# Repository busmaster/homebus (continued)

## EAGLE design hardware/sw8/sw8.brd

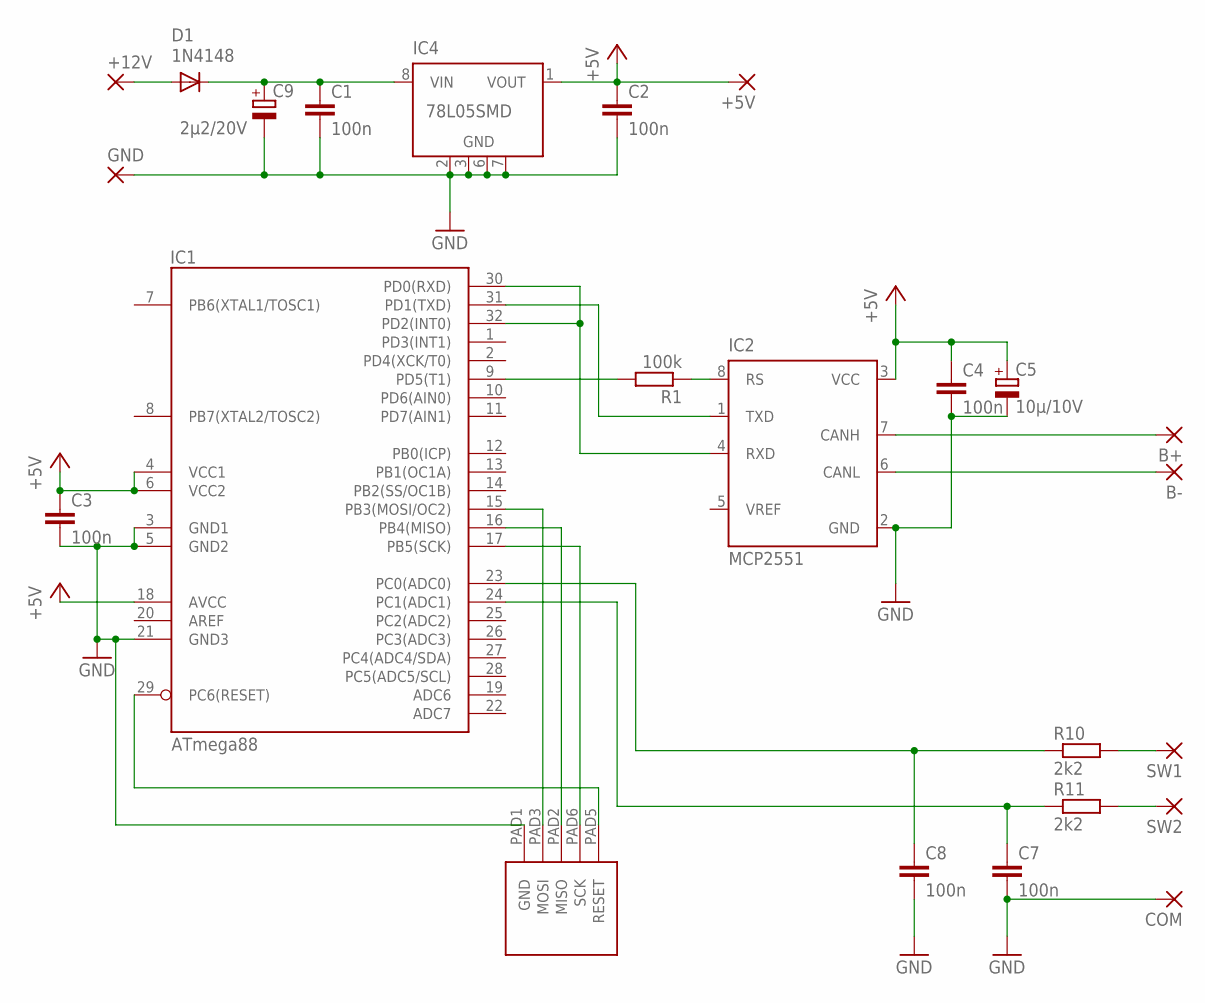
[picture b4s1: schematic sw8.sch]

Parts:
+5V, +12V: 1,6/0,8
B+: 1,6/0,8
B-: 1,6/0,8
C1, C2, C3, C4, C7, C8: 100n; C0603
C5: 10µ/10V; A/3216-18W
C9: 2µ2/20V; A/3216-18W
COM: 1,6/0,8
D1: 1N4148; SOD80C
GND: 1,6/0,8
IC1: ATmega88; TQFP32-08
IC2: MCP2551; SO8
IC4: 78L05SMD; SO08
R1: 100k; R0603
R10, R11: 2k2; R0603
SW1, SW2: 1,6/0,8
U$1: ATMEL_ISP

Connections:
+5V: +5V.1, C2.1, C3.1, C4.1, C5.+, IC1.4 (VCC1), IC1.6 (VCC2), IC1.18 (AVCC), IC2.3 (VCC), IC4.1 (VOUT)
AREF: IC1.20 (AREF)
GND: C1.2, C2.2, C3.2, C4.2, C5.-, C7.2, C8.2, C9.-, COM.1, GND.1, IC1.3 (GND1), IC1.5 (GND2), IC1.21 (GND3), IC2.2 (GND), IC4.2 (GND), IC4.3 (GND), IC4.6 (GND), IC4.7 (GND), U$1.PAD1 (GND)
MISO: IC1.16 (PB4(MISO)), U$1.PAD2 (MISO)
MOSI: IC1.15 (PB3(MOSI/OC2)), U$1.PAD3 (MOSI)
unnamed: B+.1, IC2.7 (CANH)
unnamed: B-.1, IC2.6 (CANL)
unnamed: IC1.31 (PD1(TXD)), IC2.1 (TXD)
unnamed: IC1.30 (PD0(RXD)), IC1.32 (PD2(INT0)), IC2.4 (RXD)
unnamed: IC2.8 (RS), R1.1
unnamed: IC1.9 (PD5(T1)), R1.2
unnamed: C1.1, C9.+, D1.C, IC4.8 (VIN)
unnamed: C7.1, IC1.24 (PC1(ADC1)), R11.1
unnamed: C8.1, IC1.23 (PC0(ADC0)), R10.1
unnamed: +12V.1, D1.A
unnamed: R10.2, SW1.1
unnamed: R11.2, SW2.1
RESET: IC1.29 (PC6(RESET)), U$1.PAD5 (RESET)
SCK: IC1.17 (PB5(SCK)), U$1.PAD6 (SCK)

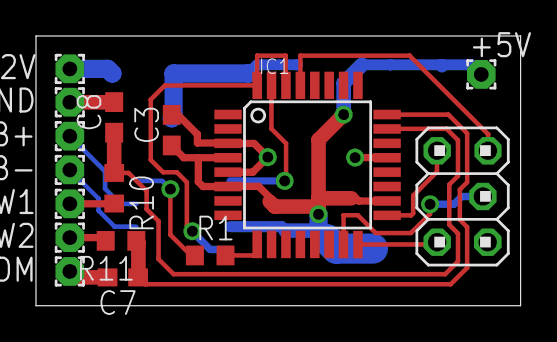
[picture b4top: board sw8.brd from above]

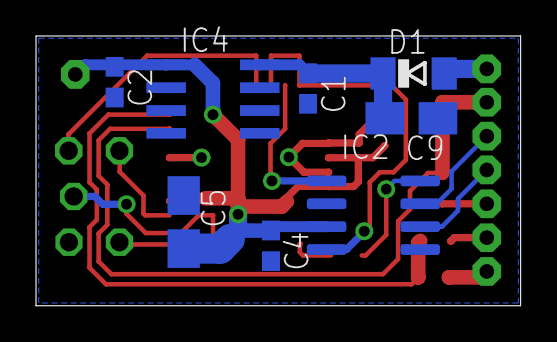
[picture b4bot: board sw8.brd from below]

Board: 2 copper layers, 26.9 x 15.0 mm, 24 parts (8 on the bottom side), 18 nets.

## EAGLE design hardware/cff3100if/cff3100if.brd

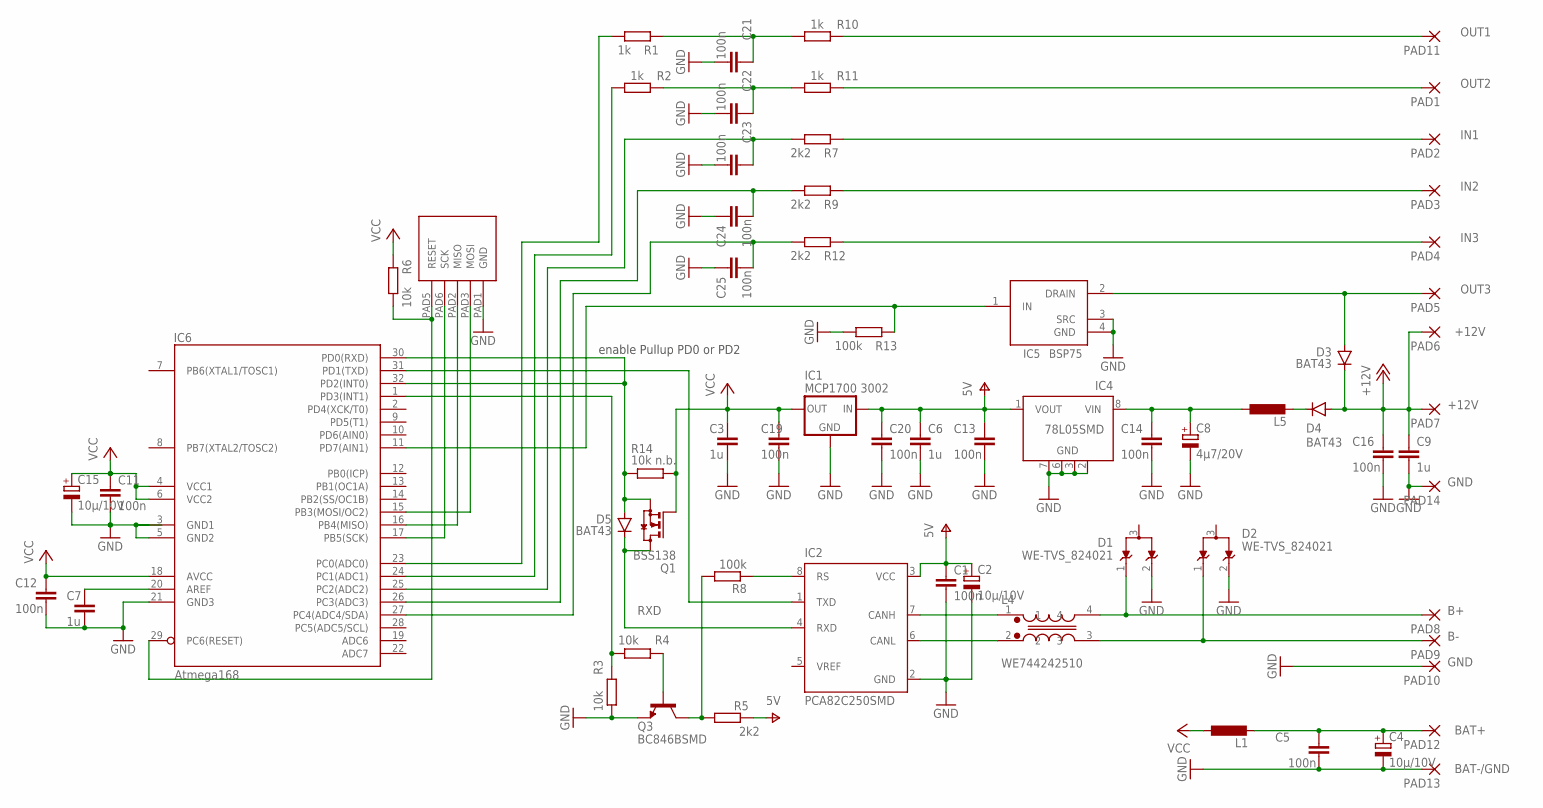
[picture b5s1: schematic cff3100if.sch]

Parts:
C1, C5, C11, C12, C13, C14, C16, C19, C20, C21, C22, C23, C24, C25: 100n; C0603
C2, C4, C15: 10µ/10V; A/3216-18W
C3, C6, C7, C9: 1u; C1206
C8: 4µ7/20V; A/3216-18W
D1, D2: WE-TVS_824021; WE-TVS_SOT23-3L
D3, D4, D5: BAT43; MINIMELF
IC1: MCP1700 3002; SOT23
IC2: PCA82C250SMD; SO8
IC4: 78L05SMD; SO08
IC5: BSP75; SOT223
IC6: Atmega168; TQFP32-08
L1, L5: L-EUL1806; L1806
L4: WE744242510; WE-SLM
PAD1, PAD2, PAD3, PAD4, PAD5, PAD7, PAD8, PAD9, PAD10, PAD11, PAD14: 1,6/0,9
PAD6: +12V; 1,6/0,9
PAD12: BAT+; 1,6/0,9
PAD13: BAT-/GND; 1,6/0,9
Q1: BSS138; SOT23
Q3: BC846BSMD; SOT23
R1, R2, R10, R11: 1k; R0603
R3, R4, R6: 10k; R0603
R5, R7, R9, R12: 2k2; R0603
R8, R13: 100k; R0603
R14: 10k n.b.; R0603
U$2: ATMEL_ISP

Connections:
+12V: C9.1, C16.1, D3.C, D4.A, PAD6.1, PAD7.1
B+: D1.1, L4.4, PAD8.1
B-: D2.1, L4.3, PAD9.1
GND: C1.2, C2.-, C3.2, C4.-, C5.2, C6.2, C7.2, C8.-, C9.2, C11.2, C12.2, C13.2, C14.2, C15.-, C16.2, C19.2, C20.2, C21.2, C22.2, C23.2, C24.1, C25.1, D1.2, D2.2, IC1.1 (GND), IC2.2 (GND), IC4.2 (GND), IC4.3 (GND), IC4.6 (GND), IC4.7 (GND), IC5.3 (SRC), IC5.4 (GND), IC6.3 (GND1), IC6.5 (GND2), IC6.21 (GND3), PAD10.1, PAD13.1, PAD14.1, Q3.2 (E), R3.2, R13.2, U$2.PAD1 (GND)
IN1: PAD2.1, R7.1
IN2: PAD3.1, R9.1
IN3: PAD4.1, R12.1
unnamed: IC6.29 (PC6(RESET)), R6.2, U$2.PAD5 (RESET)
unnamed: C4.+, C5.1, L1.2, PAD12.1
unnamed: IC6.1 (PD3(INT1)), R3.1, R4.2
unnamed: D4.C, L5.2
unnamed: IC6.23 (PC0(ADC0)), R1.2
unnamed: IC6.24 (PC1(ADC1)), R2.2
unnamed: C21.1, R1.1, R10.2
unnamed: C22.1, R2.1, R11.2
unnamed: IC2.7 (CANH), L4.1
unnamed: Q3.3 (C), R5.1, R8.2
unnamed: Q3.1 (B), R4.1
unnamed: C23.1, IC6.25 (PC2(ADC2)), R7.2
unnamed: C24.2, IC6.26 (PC3(ADC3)), R9.2
unnamed: C25.2, IC6.27 (PC4(ADC4/SDA)), R12.2
unnamed: IC2.1 (TXD), IC6.31 (PD1(TXD))
unnamed: IC2.6 (CANL), L4.2
unnamed: D5.A, IC6.30 (PD0(RXD)), IC6.32 (PD2(INT0)), Q1.2 (S), R14.2
unnamed: IC5.1 (IN), IC6.11 (PD7(AIN1)), R13.1
unnamed: IC6.17 (PB5(SCK)), U$2.PAD6 (SCK)
unnamed: IC6.15 (PB3(MOSI/OC2)), U$2.PAD3 (MOSI)
unnamed: IC6.16 (PB4(MISO)), U$2.PAD2 (MISO)
unnamed: C7.1, IC6.20 (AREF)
unnamed: IC2.8 (RS), R8.1
unnamed: C8.+, C14.1, IC4.8 (VIN), L5.1
OUT1: PAD11.1, R10.1
OUT2: PAD1.1, R11.1
OUT3: D3.A, IC5.2 (DRAIN), PAD5.1
RXD: D5.C, IC2.4 (RXD), Q1.3 (D)
V+: C1.1, C2.+, C6.1, C13.1, C20.1, IC1.3 (IN), IC2.3 (VCC), IC4.1 (VOUT), R5.2
VCC: C3.1, C11.1, C12.1, C15.+, C19.1, IC1.2 (OUT), IC6.4 (VCC1), IC6.6 (VCC2), IC6.18 (AVCC), L1.1, Q1.1 (G), R6.1, R14.1

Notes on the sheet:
enable Pullup PD0 or PD2

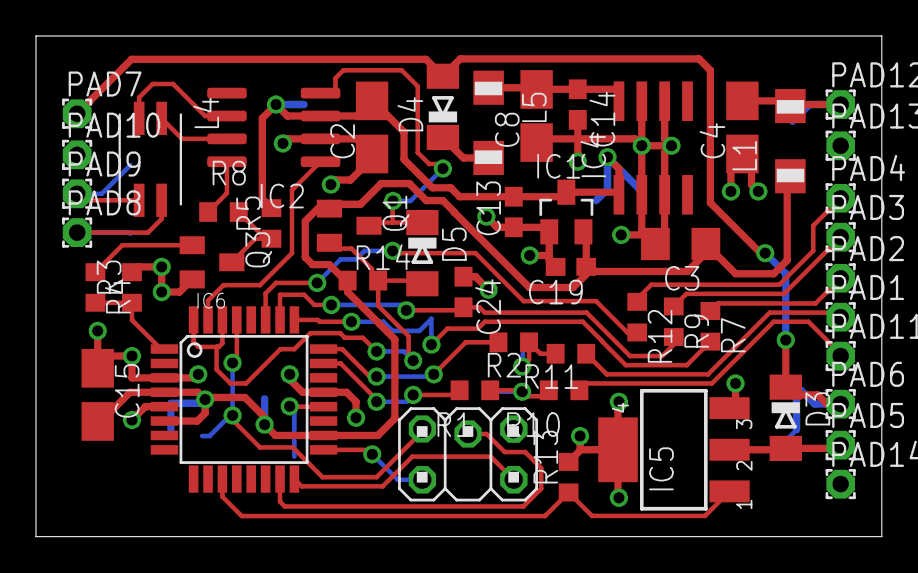
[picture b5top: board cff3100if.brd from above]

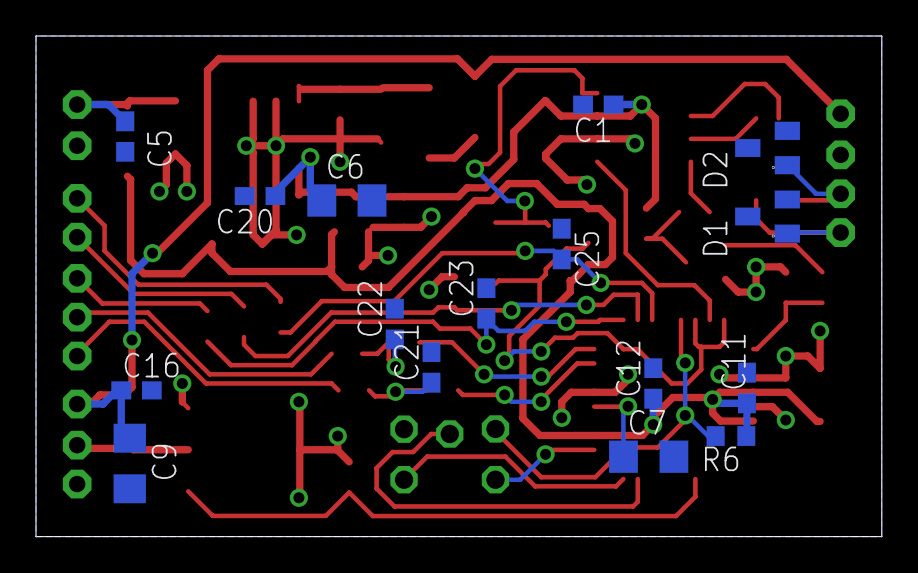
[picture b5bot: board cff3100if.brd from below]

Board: 2 copper layers, 47.0 x 27.8 mm, 66 parts (16 on the bottom side), 37 nets.

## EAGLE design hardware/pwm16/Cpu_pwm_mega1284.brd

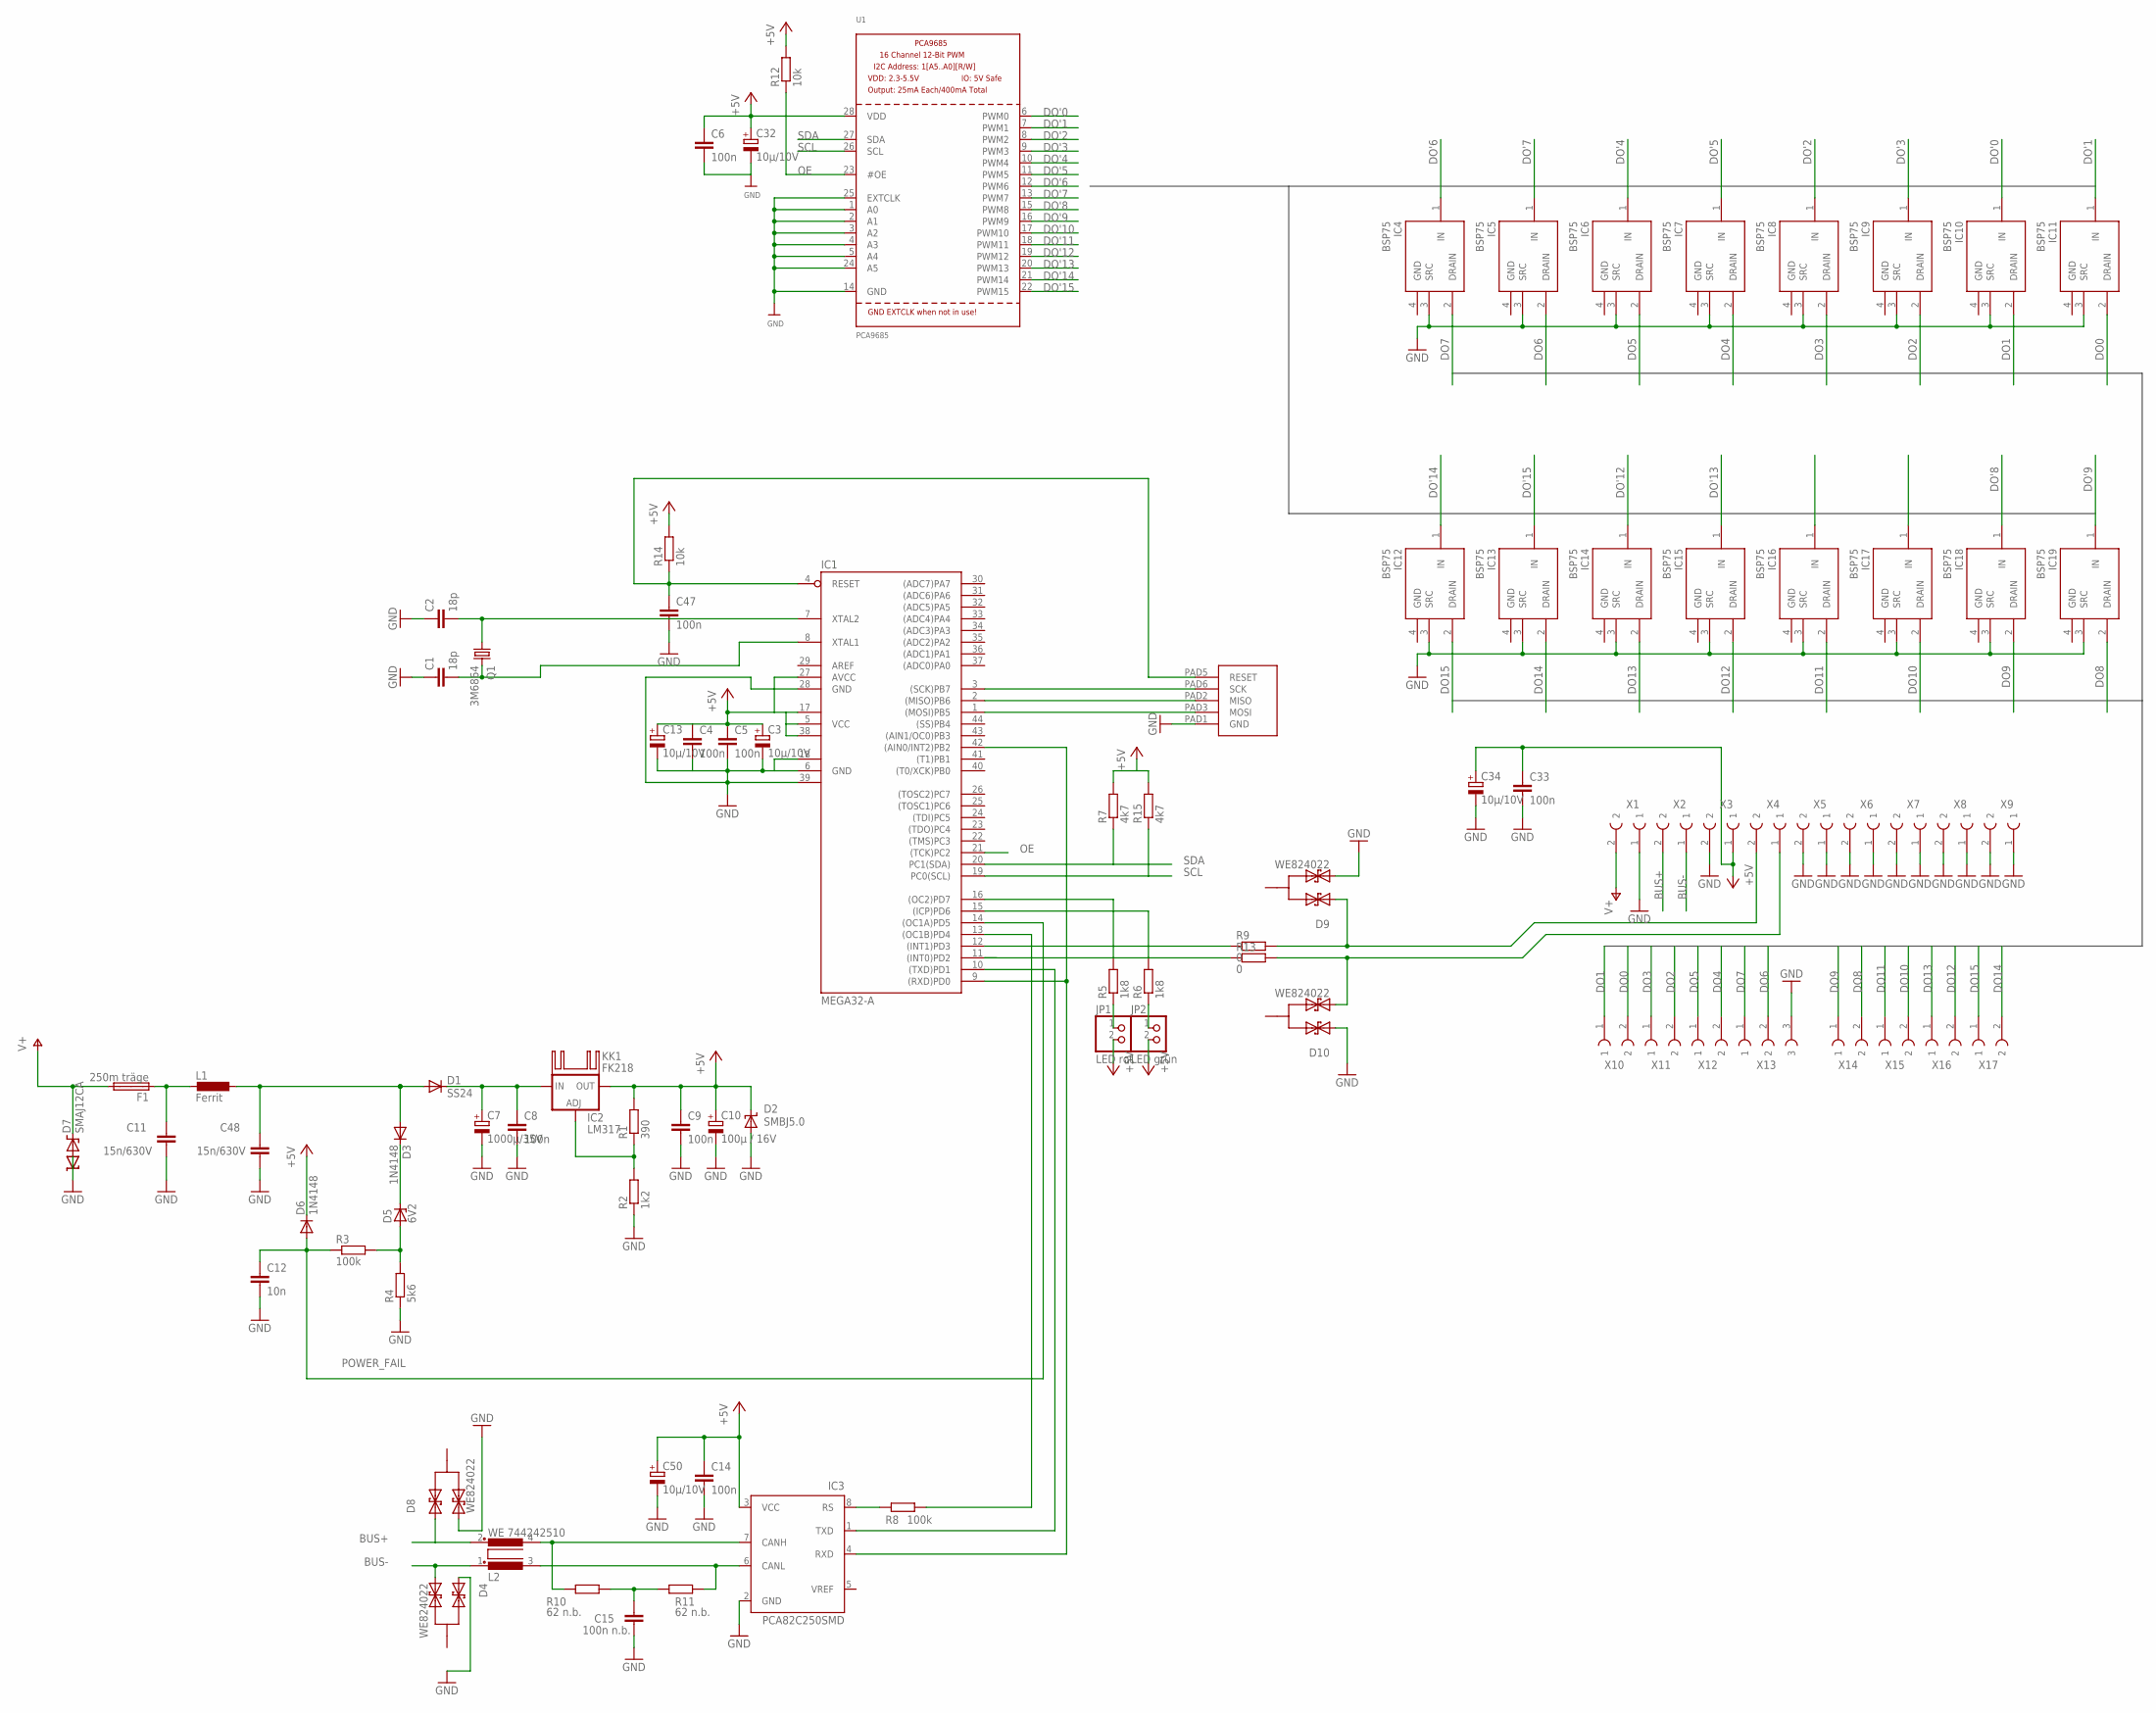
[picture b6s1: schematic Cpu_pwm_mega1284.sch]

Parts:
C1, C2: 18p; C0603K
C3, C13, C32, C34, C50: 10µ/10V; A/3216-18W
C4, C5, C6, C8, C9, C14, C33, C47: 100n; C0603K
C7: 1000µ/35V; E5-13
C10: 100µ / 16V; SMC_D
C11, C48: 15n/630V; C1210K
C12: 10n; C0603K
C15: 100n n.b.; C0603K
D1: SS24; SMB
D2: SMBJ5.0; SMBJ
D3, D6: 1N4148; MINIMELF
D4, D8, D9, D10: WE824022; SOT23
D5: 6V2; SOD80C
D7: SMAJ12CA; DO-214AC
F1: 250m träge; SHK20L
IC1: MEGA32-A; TQFP44
IC2: LM317; 317TS
IC3: PCA82C250SMD; SO8
IC4, IC5, IC6, IC7, IC8, IC9, IC10, IC11, IC12, IC13, IC14, IC15, IC16, IC17, IC18, IC19: BSP75; SOT223
JP1: LED rot; 1X02
JP2: LED grün; 1X02
KK1: FK218
L1: Ferrit; L1806
L2: WE 744242510; 744242510
Q1: 3M6864; HC49UP
R1: 390; R0603
R2: 1k2; R0603
R3, R8: 100k; R0603
R4: 5k6; R0603
R5, R6: 1k8; R0603
R7, R15: 4k7; R0603
R9, R13: 0; R0603
R10, R11: 62 n.b.; R1210
R12, R14: 10k; R0603
U1: PCA9685; TSSOP28
U$1: ATMEL_ISP
X1, X2, X3, X4, X5, X6, X7, X8, X9, X10, X11, X12, X14, X15, X16, X17: AR-KLEMME_508_2POLPTR; W237-2E
X13: AR-KLEMME_508_3POLPTR; W237-3E

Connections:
+5V: C3.+, C4.1, C5.1, C6.1, C9.1, C10.+, C13.+, C14.1, C32.+, C33.1, C34.+, C50.+, D2.C, D6.C, IC1.5 (VCC), IC1.17 (VCC1), IC1.27 (AVCC), IC1.38 (VCC2), IC2.2 (OUT), IC3.3 (VCC), JP1.2, JP2.2, R1.2, R7.2, R12.2, R14.2, R15.2, U1.28 (VDD), X3.1
/RESET: C47.1, IC1.4 (RESET), R14.1, U$1.PAD5 (RESET)
BUS+: D8.1, L2.2, X2.2
BUS-: D4.2, L2.1, X2.1
DO0: IC11.2 (DRAIN), X10.2
DO1: IC10.2 (DRAIN), X10.1
DO2: IC9.2 (DRAIN), X11.2
DO3: IC8.2 (DRAIN), X11.1
DO4: IC7.2 (DRAIN), X12.2
DO5: IC6.2 (DRAIN), X12.1
DO6: IC5.2 (DRAIN), X13.2
DO7: IC4.2 (DRAIN), X13.1
DO8: IC19.2 (DRAIN), X14.2
DO9: IC18.2 (DRAIN), X14.1
DO10: IC17.2 (DRAIN), X15.2
DO11: IC16.2 (DRAIN), X15.1
DO12: IC15.2 (DRAIN), X16.2
DO13: IC14.2 (DRAIN), X16.1
DO14: IC13.2 (DRAIN), X17.2
DO15: IC12.2 (DRAIN), X17.1
DO'0: IC10.1 (IN), U1.6 (PWM0)
DO'1: IC11.1 (IN), U1.7 (PWM1)
DO'2: IC8.1 (IN), U1.8 (PWM2)
DO'3: IC9.1 (IN), U1.9 (PWM3)
DO'4: IC6.1 (IN), U1.10 (PWM4)
DO'5: IC7.1 (IN), U1.11 (PWM5)
DO'6: IC4.1 (IN), U1.12 (PWM6)
DO'7: IC5.1 (IN), U1.13 (PWM7)
DO'8: IC18.1 (IN), U1.15 (PWM8)
DO'9: IC19.1 (IN), U1.16 (PWM9)
DO'10: IC16.1 (IN), U1.17 (PWM10)
DO'11: IC17.1 (IN), U1.18 (PWM11)
DO'12: IC14.1 (IN), U1.19 (PWM12)
DO'13: IC15.1 (IN), U1.20 (PWM13)
DO'14: IC12.1 (IN), U1.21 (PWM14)
DO'15: IC13.1 (IN), U1.22 (PWM15)
GND: C1.1, C2.1, C3.-, C4.2, C5.2, C6.2, C7.-, C8.2, C9.2, C10.-, C11.2, C12.2, C13.-, C14.2, C15.1, C32.-, C33.2, C34.-, C47.2, C48.2, C50.-, D2.A, D4.1, D7.A, D8.2, D9.2, D10.1, IC1.6 (GND), IC1.18 (GND1), IC1.28 (GND), IC1.39 (GND2), IC3.2 (GND), IC4.3 (SRC), IC5.3 (SRC), IC6.3 (SRC), IC7.3 (SRC), IC8.3 (SRC), IC9.3 (SRC), IC10.3 (SRC), IC11.3 (SRC), IC12.3 (SRC), IC13.3 (SRC), IC14.3 (SRC), IC15.3 (SRC), IC16.3 (SRC), IC17.3 (SRC), IC18.3 (SRC), IC19.3 (SRC), R2.1, R4.1, U1.1 (A0), U1.2 (A1), U1.3 (A2), U1.4 (A3), U1.5 (A4), U1.14 (GND), U1.24 (A5), U1.25 (EXTCLK), U$1.PAD1 (GND), X1.1, X3.2, X5.1, X5.2, X6.1, X6.2, X7.1, X7.2, X8.1, X8.2, X9.1, X9.2, X13.3
MISO: IC1.2 ((MISO)PB6), U$1.PAD2 (MISO)
MOSI: IC1.1 ((MOSI)PB5), U$1.PAD3 (MOSI)
unnamed: C11.1, F1.1A, L1.2
unnamed: D3.C, D5.C
unnamed: D5.A, R3.2, R4.2
unnamed: C1.2, IC1.8 (XTAL1), Q1.2
unnamed: C2.2, IC1.7 (XTAL2), Q1.1
unnamed: IC3.8 (RS), R8.2
unnamed: IC1.13 ((OC1B)PD4), R8.1
unnamed: IC2.1 (ADJ), R1.1, R2.2
unnamed: IC3.6 (CANL), L2.3, R11.1
unnamed: IC3.7 (CANH), L2.4, R10.2
unnamed: C48.1, D1.A, D3.A, L1.1
unnamed: C7.+, C8.1, D1.C, IC2.3 (IN)
unnamed: IC1.11 ((INT0)PD2), R13.1
unnamed: IC1.12 ((INT1)PD3), R9.1
unnamed: C15.2, R10.1, R11.2
unnamed: JP1.1, R5.1
unnamed: JP2.1, R6.1
unnamed: IC1.16 ((OC2)PD7), R5.2
unnamed: IC1.15 ((ICP)PD6), R6.2
OE: IC1.21 ((TCK)PC2), R12.1, U1.23 (#OE)
POWER_FAIL: C12.1, D6.A, IC1.14 ((OC1A)PD5), R3.1
RXD: IC1.9 ((RXD)PD0), IC1.42 ((AIN0/INT2)PB2), IC3.4 (RXD)
RXD1: D10.2, R13.2, X4.1
SCK: IC1.3 ((SCK)PB7), U$1.PAD6 (SCK)
SCL: IC1.19 (PC0(SCL)), R15.1, U1.26 (SCL)
SDA: IC1.20 (PC1(SDA)), R7.1, U1.27 (SDA)
TSD1: D9.1, R9.2, X4.2
TXD: IC1.10 ((TXD)PD1), IC3.1 (TXD)
V+: D7.C, F1.2A, X1.2

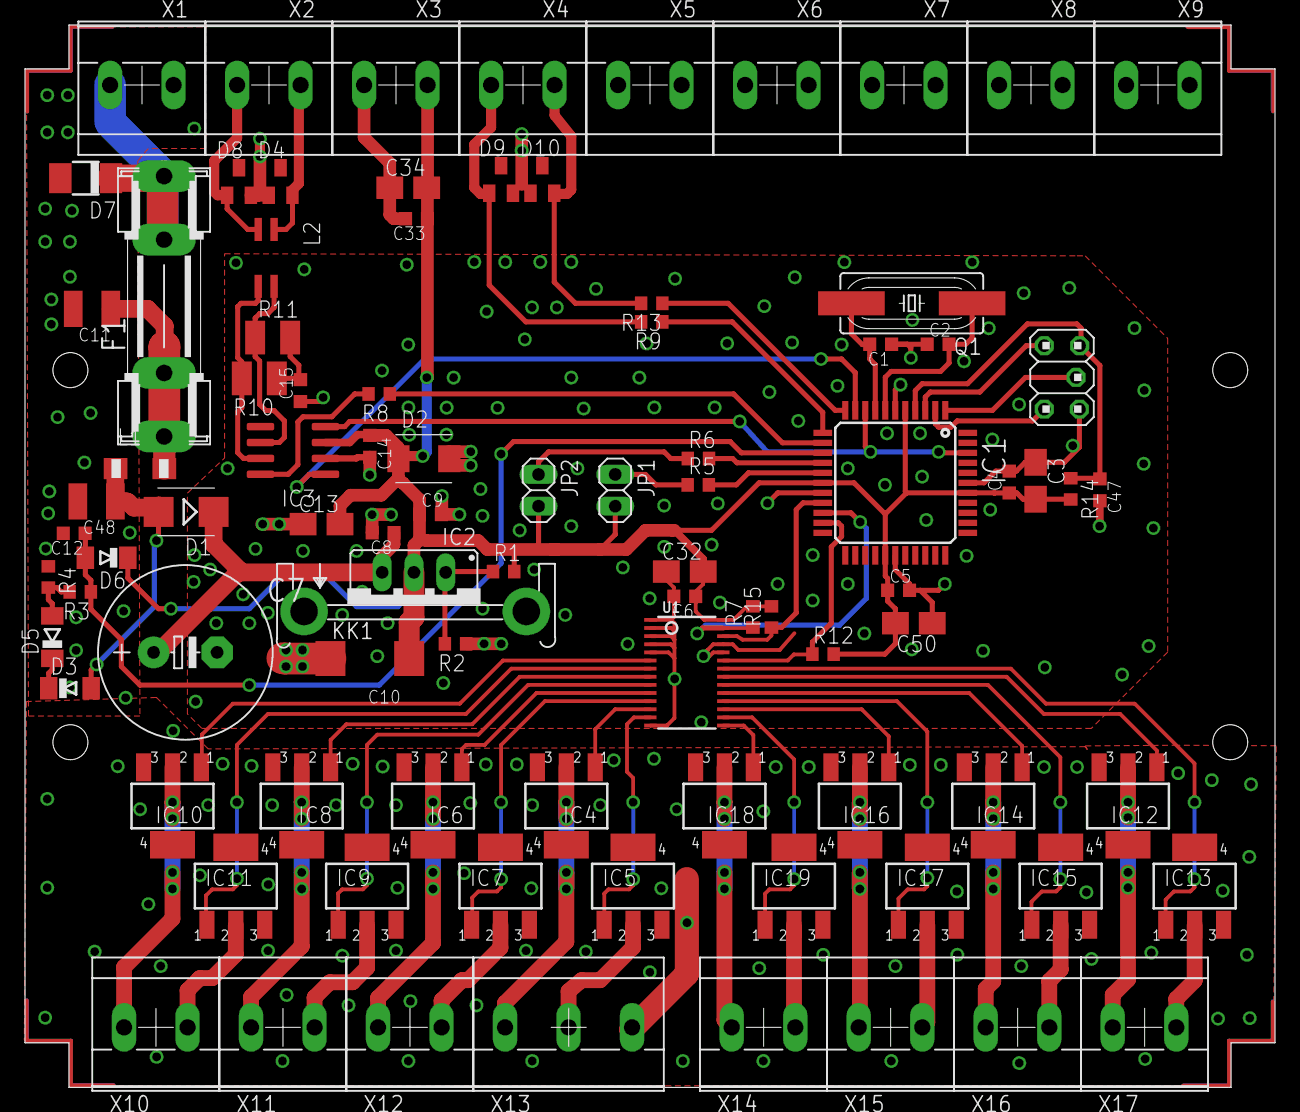
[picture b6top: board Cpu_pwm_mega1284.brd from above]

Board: 2 copper layers, 100.0 x 85.0 mm, 92 parts (0 on the bottom side), 68 nets.

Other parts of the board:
U$3: GEHÄUSE_MR6

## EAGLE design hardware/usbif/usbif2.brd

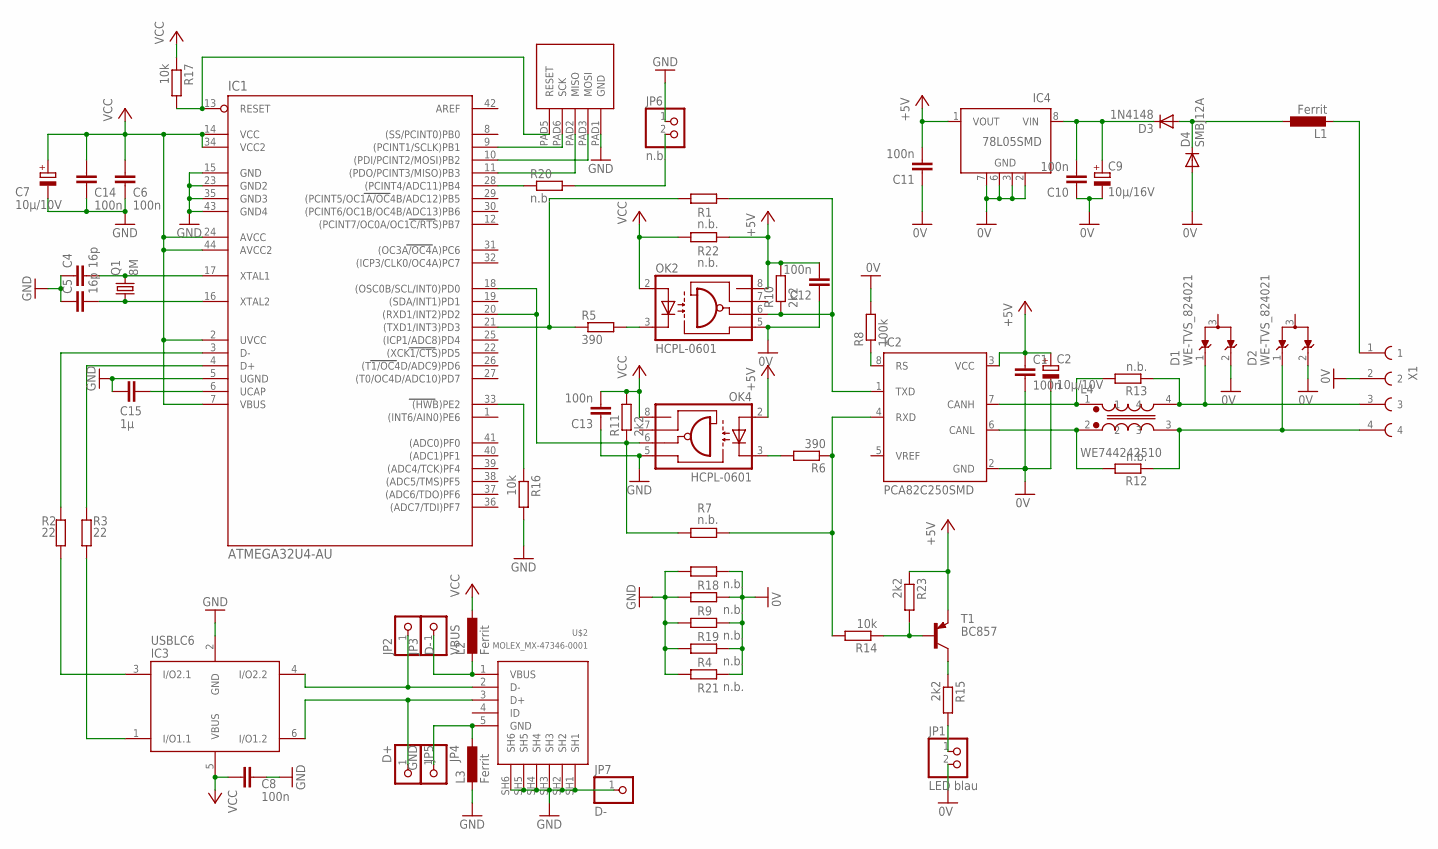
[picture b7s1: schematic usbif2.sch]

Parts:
C1, C6, C8, C10, C11, C12, C13, C14: 100n; C0603
C2, C7: 10µ/10V; A/3216-18W
C4, C5: 16p; C0603
C9: 10µ/16V; A/3216-18W
C15: 1µ; C1210K
D1, D2: WE-TVS_824021; WE-TVS_SOT23-3L
D3: 1N4148; SOD80C
D4: SMBJ12A; SMB
IC1: ATMEGA32U4-AU; TQFP44
IC2: PCA82C250SMD; SO8
IC3: USBLC6; SOT23-6L
IC4: 78L05SMD; SO08
JP1: LED blau; 1X02
JP2, JP7: D-; 1X01
JP3: VBUS; 1X01
JP4: GND; 1X01
JP5: D+; 1X01
JP6: n.b.; 1X02
L1, L2, L3: Ferrit; L1806
L4: WE744242510; WE-SLM
OK2, OK4: HCPL-0601; SOIC08
Q1: 8M; SM49
R1, R4, R7, R9, R18, R19, R21, R22: n.b.; MINI_MELF-0204R
R2, R3: 22; R0603
R5, R6: 390; R0603
R8: 100k; R0603
R10, R11, R15, R23: 2k2; R0603
R12, R13, R20: n.b.; R0603
R14, R16, R17: 10k; R0603
T1: BC857; SOT323-BEC
U$1: ATMEL_ISP
U$2: MOLEX_MX-47346-0001
X1: DEGSON_15EDGRC-3.5_4

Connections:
0V: C1.2, C2.-, C9.-, C10.1, C11.1, C12.1, D1.2, D2.2, D4.A, IC2.2 (GND), IC4.2 (GND), IC4.3 (GND), IC4.6 (GND), IC4.7 (GND), JP1.2, OK2.5 (GND), R4.1, R8.2, R9.1, R18.1, R19.1, R21.1, X1.2
#RESET: IC1.13 (RESET), R17.2, U$1.PAD5 (RESET)
+5V: C1.1, C2.+, C11.2, C12.2, IC2.3 (VCC), IC4.1 (VOUT), OK2.8 (VCC), OK4.2 (A), R10.2, R22.1, R23.1, T1.E
+12V: L1.2, X1.1
B+: D1.1, L4.4, R13.1, X1.3
B-: D2.1, L4.3, R12.1, X1.4
D+: IC3.6 (I/O1.2), JP5.1, U$2.3 (D+)
D-: IC3.4 (I/O2.2), JP2.1, U$2.2 (D-)
GND: C4.1, C5.1, C6.1, C7.-, C8.1, C13.1, C14.1, C15.2, IC1.5 (UGND), IC1.15 (GND), IC1.23 (GND2), IC1.35 (GND3), IC1.43 (GND4), IC3.2 (GND), JP6.1, JP7.1, L3.2, OK4.5 (GND), R4.2, R9.2, R16.2, R18.2, R19.2, R21.2, U$1.PAD1 (GND), U$2.SH1, U$2.SH2, U$2.SH3, U$2.SH4, U$2.SH5, U$2.SH6
unnamed: OK2.3 (C), R5.2
unnamed: IC1.18 ((OSC0B/SCL/INT0)PD0), IC1.20 ((RXD1/INT2)PD2), OK4.6 (VO), R7.2, R11.1
unnamed: IC2.1 (TXD), OK2.6 (VO), R1.1, R10.1
unnamed: IC2.4 (RXD), R6.1, R7.1, R14.2
unnamed: IC1.10 ((PDI/PCINT2/MOSI)PB2), U$1.PAD3 (MOSI)
unnamed: IC1.11 ((PDO/PCINT3/MISO)PB3), U$1.PAD2 (MISO)
unnamed: IC1.9 ((PCINT1/SCLK)PB1), U$1.PAD6 (SCK)
unnamed: IC1.4 (D+), R3.1
unnamed: IC2.7 (CANH), L4.1, R13.2
unnamed: C15.1, IC1.6 (UCAP)
unnamed: IC1.3 (D-), R2.1
unnamed: IC3.1 (I/O1.1), R3.2
unnamed: IC3.3 (I/O2.1), R2.2
unnamed: C4.2, IC1.17 (XTAL1), Q1.2
unnamed: C5.2, IC1.16 (XTAL2), Q1.1
unnamed: IC2.6 (CANL), L4.2, R12.2
unnamed: JP6.2, R20.2
unnamed: IC1.28 ((PCINT4/ADC11)PB4), R20.1
unnamed: D3.A, D4.C, L1.1
unnamed: C9.+, C10.2, D3.C, IC4.8 (VIN)
unnamed: OK4.3 (C), R6.2
unnamed: R15.1, T1.C
unnamed: IC1.33 ((HWB)PE2), R16.1
unnamed: R14.1, R23.2, T1.B
unnamed: JP1.1, R15.2
unnamed: IC2.8 (RS), R8.1
unnamed: JP4.1, L3.1, U$2.5 (GND)
unnamed: IC1.21 ((TXD1/INT3)PD3), R1.2, R5.1
VBUS: JP3.1, L2.2, U$2.1 (VBUS)
VCC: C6.2, C7.+, C8.2, C13.2, C14.2, IC1.2 (UVCC), IC1.7 (VBUS), IC1.14 (VCC), IC1.24 (AVCC), IC1.34 (VCC2), IC1.44 (AVCC2), IC3.5 (VBUS), L2.1, OK2.2 (A), OK4.8 (VCC), R11.2, R17.1, R22.2

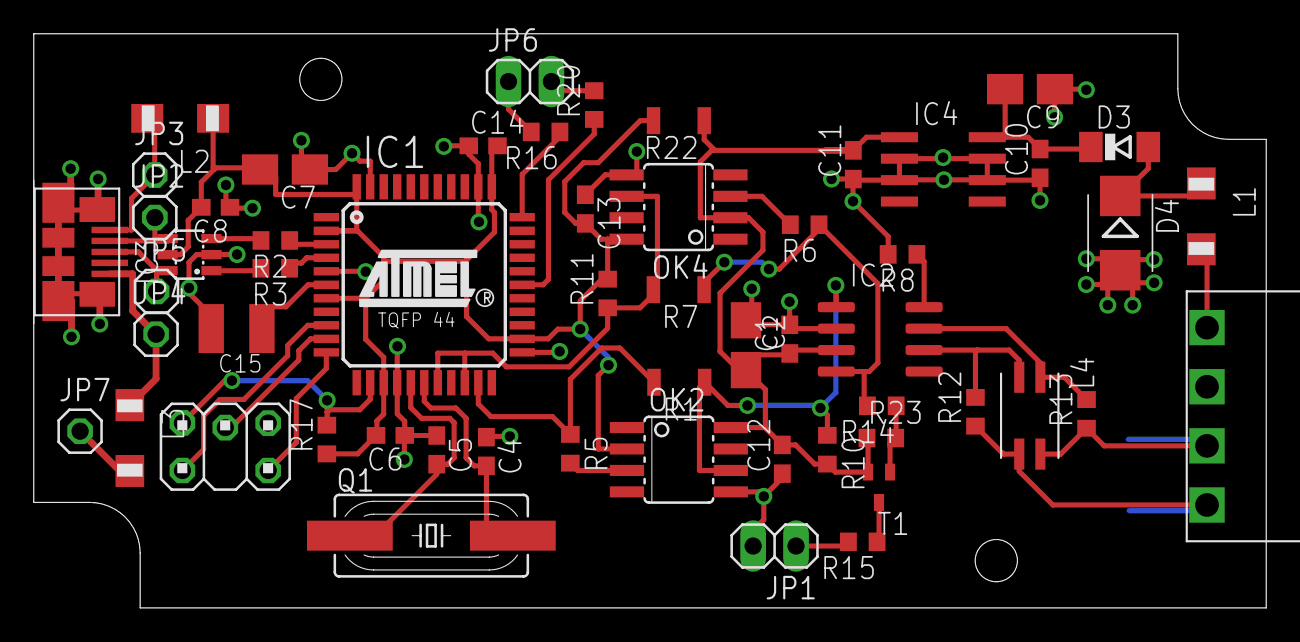
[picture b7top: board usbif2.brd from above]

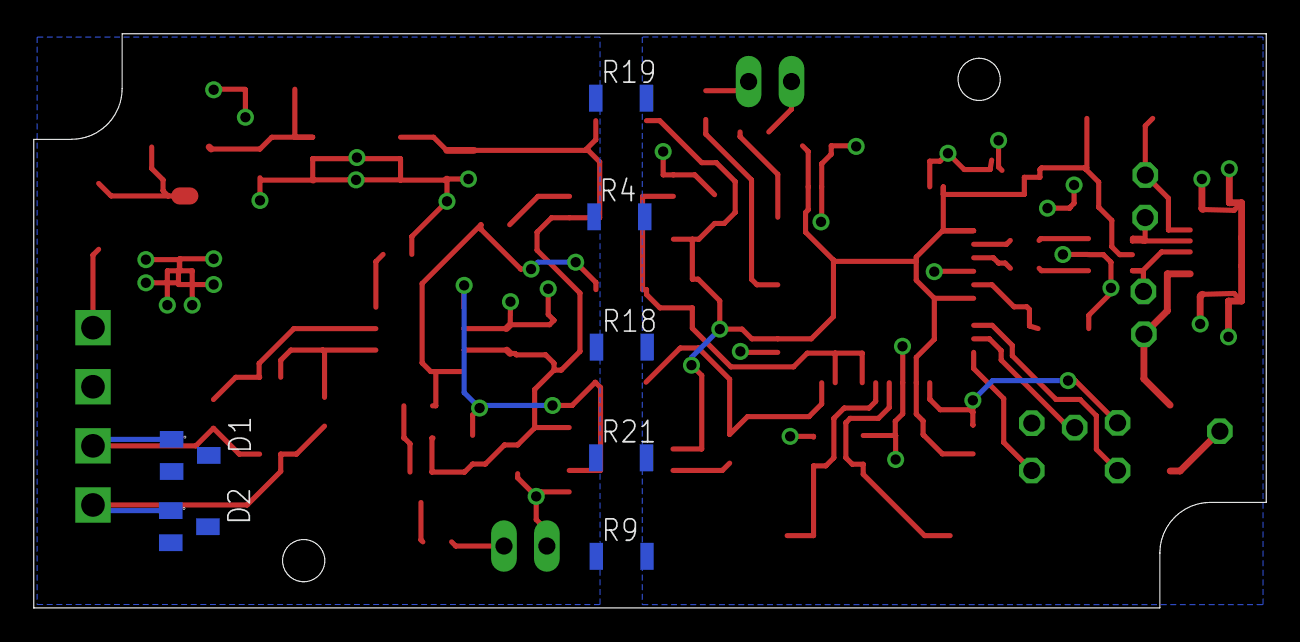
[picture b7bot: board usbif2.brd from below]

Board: 2 copper layers, 73.0 x 34.0 mm, 63 parts (7 on the bottom side), 39 nets.

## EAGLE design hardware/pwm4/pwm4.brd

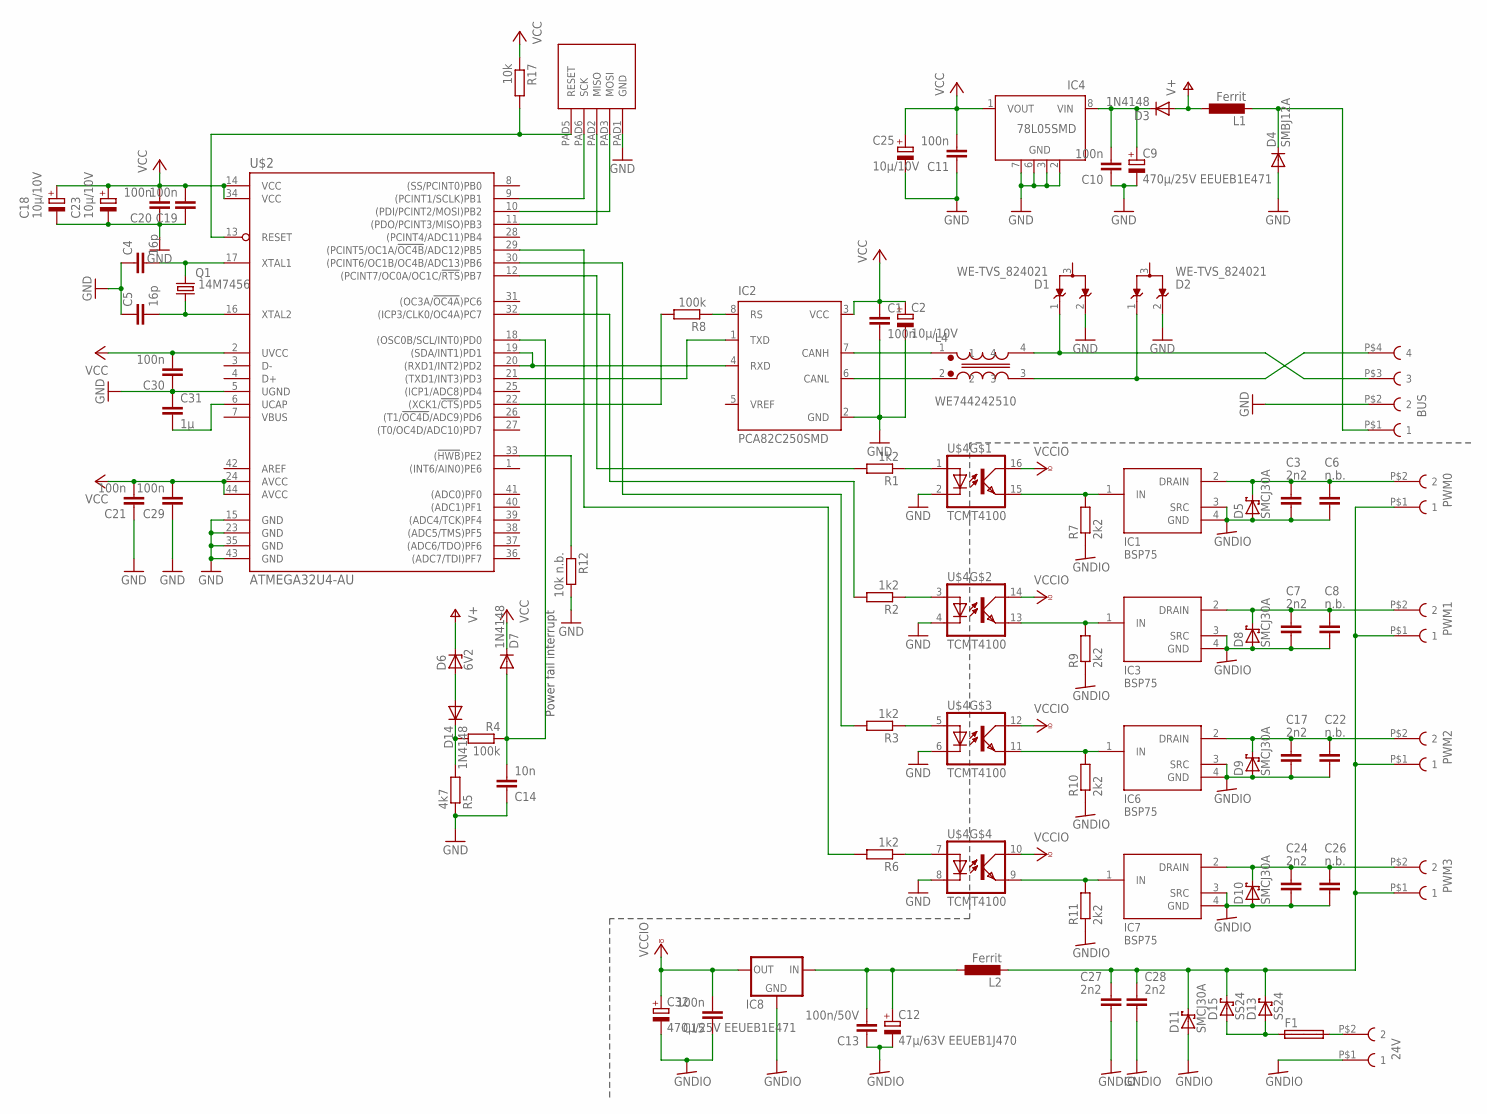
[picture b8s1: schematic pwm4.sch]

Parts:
24V: TBG-3.5-PW-2P
BUS: TBG-3.5-PW-4P
C1, C10, C11, C15, C19, C20, C21, C29, C30: 100n; C0603
C2, C18, C23, C25: 10µ/10V; A/3216-18W
C3, C7, C17, C24, C27, C28: 2n2; C025-040X050
C4, C5: 16p; C0603
C6, C8, C22, C26: n.b.; C025-040X050
C9, C32: 470µ/25V EEUEB1E471; E5-10,5
C12: 47µ/63V EEUEB1J470; E3,5-8
C13: 100n/50V; C0603
C14: 10n; C0603
C31: 1µ; C1210K
D1, D2: WE-TVS_824021; WE-TVS_SOT23-3L
D3, D7, D14: 1N4148; SOD80C
D4: SMBJ12A; SMB
D5, D8, D9, D10, D11: SMCJ30A; SMC
D6: 6V2; SOD80C
D13, D15: SS24; SMB
F1: SHK20L
IC1, IC3, IC6, IC7: BSP75; SOT223
IC2: PCA82C250SMD; SO8
IC4: 78L05SMD; SO08
IC8: 78XXS
L1, L2: Ferrit; L1806
L4: WE744242510; WE-SLM
PWM0, PWM1, PWM2, PWM3: TBG-3.5-PW-2P
Q1: 14M7456; SM49
R1, R2, R3, R6: 1k2; R0603
R4, R8: 100k; R0603
R5: 4k7; R0603
R7, R9, R10, R11: 2k2; R0603
R12: 10k n.b.; R0603
R17: 10k; R0603
U$1: ATMEL_ISP
U$2: ATMEGA32U4-AU; TQFP44
U$4: TCMT4100; SOIC16

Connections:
#RESET: R17.2, U$1.PAD5 (RESET), U$2.13 (RESET)
B+: BUS.P$3 (3), D1.1, L4.4
B-: BUS.P$4 (4), D2.1, L4.3
GND: BUS.P$2 (2), C1.2, C2.-, C4.1, C5.1, C9.-, C10.1, C11.1, C14.1, C18.-, C19.1, C20.1, C21.1, C23.-, C25.-, C29.1, C30.1, C31.1, D1.2, D2.2, D4.A, IC2.2 (GND), IC4.2 (GND), IC4.3 (GND), IC4.6 (GND), IC4.7 (GND), R5.1, R12.2, U$1.PAD1 (GND), U$2.5 (UGND), U$2.15 (GND), U$2.23 (GND), U$2.35 (GND), U$2.43 (GND), U$4.2 (C), U$4.4 (C), U$4.6 (C), U$4.8 (C)
GNDIO: 24V.P$1 (1), C3.1, C6.1, C7.1, C8.1, C12.-, C13.1, C15.1, C17.1, C22.1, C24.1, C26.1, C27.1, C28.1, C32.-, D5.A, D8.A, D9.A, D10.A, D11.A, IC1.3 (SRC), IC1.4 (GND), IC3.3 (SRC), IC3.4 (GND), IC6.3 (SRC), IC6.4 (GND), IC7.3 (SRC), IC7.4 (GND), IC8.GND, R7.1, R9.1, R10.1, R11.1
MISO: U$1.PAD2 (MISO), U$2.11 ((PDO/PCINT3/MISO)PB3)
MOSI: U$1.PAD3 (MOSI), U$2.10 ((PDI/PCINT2/MOSI)PB2)
unnamed: R8.2, U$2.22 ((XCK1/!CTS!)PD5)
unnamed: C3.2, C6.2, D5.C, IC1.2 (DRAIN), PWM0.P$2 (2)
unnamed: IC2.1 (TXD), U$2.21 ((TXD1/INT3)PD3)
unnamed: C9.+, C10.2, D3.C, IC4.8 (VIN)
unnamed: C7.2, C8.2, D8.C, IC3.2 (DRAIN), PWM1.P$2 (2)
unnamed: IC2.7 (CANH), L4.1
unnamed: R1.1, U$4.1 (A)
unnamed: IC2.4 (RXD), U$2.19 ((SDA/INT1)PD1), U$2.20 ((RXD1/INT2)PD2)
unnamed: C17.2, C22.2, D9.C, IC6.2 (DRAIN), PWM2.P$2 (2)
unnamed: C24.2, C26.2, D10.C, IC7.2 (DRAIN), PWM3.P$2 (2)
unnamed: C4.2, Q1.2, U$2.17 (XTAL1)
unnamed: C5.2, Q1.1, U$2.16 (XTAL2)
unnamed: IC2.6 (CANL), L4.2
unnamed: C12.+, C13.2, IC8.IN, L2.1
unnamed: C27.2, C28.2, D11.C, D13.C, D15.C, L2.2, PWM0.P$1 (1), PWM1.P$1 (1), PWM2.P$1 (1), PWM3.P$1 (1)
unnamed: BUS.P$1 (1), D4.C, L1.2
unnamed: 24V.P$2 (2), F1.2A
unnamed: D6.A, D14.A
unnamed: D13.A, D15.A, F1.1A
unnamed: R2.1, U$4.3 (A)
unnamed: R3.1, U$4.5 (A)
unnamed: R6.1, U$4.7 (A)
unnamed: IC2.8 (RS), R8.1
unnamed: D14.C, R4.2, R5.2
unnamed: IC1.1 (IN), R7.2, U$4.15 (EMIT)
unnamed: IC3.1 (IN), R9.2, U$4.13 (EMIT)
unnamed: IC6.1 (IN), R10.2, U$4.11 (EMIT)
unnamed: IC7.1 (IN), R11.2, U$4.9 (EMIT)
unnamed: C31.2, U$2.6 (UCAP)
unnamed: R12.1, U$2.33 ((!HWB!)PE2)
unnamed: C14.2, D7.A, R4.1, U$2.18 ((OSC0B/SCL/INT0)PD0)
PWM0: R1.2, U$2.12 ((PCINT7/OC0A/OC1C/!RTS!)PB7)
PWM1: R2.2, U$2.32 ((ICP3/CLK0/OC4A)PC7)
PWM2: R3.2, U$2.30 ((PCINT6/OC1B/OC4B/ADC13)PB6)
PWM3: R6.2, U$2.29 ((PCINT5/OC1A/!OC4B!/ADC12)PB5)
SCK: U$1.PAD6 (SCK), U$2.9 ((PCINT1/SCLK)PB1)
V+: D3.A, D6.C, L1.1
VCC: C1.1, C2.+, C11.2, C18.+, C19.2, C20.2, C21.2, C23.+, C25.+, C29.2, C30.2, D7.C, IC2.3 (VCC), IC4.1 (VOUT), R17.1, U$2.2 (UVCC), U$2.14 (VCC), U$2.24 (AVCC), U$2.34 (VCC), U$2.44 (AVCC)
VCCIO: C15.2, C32.+, IC8.OUT, U$4.10 (COL), U$4.12 (COL), U$4.14 (COL), U$4.16 (COL)

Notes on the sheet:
Power fail interrupt
